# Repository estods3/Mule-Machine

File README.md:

# mule_machine
A drinkbot for making Moscow Mules

## Design File Structure

### SW
ATmega328 microcontroller code.
  * Pin Assignments
  * Bootup Animation
  * Standby Animation
  * Potentiometer Calibration Controls
  * Cup-Sensor Detection
  * Pump Control and LED animation

### HW

#### cad

Sketchup File - 3D model

LightBurn laser engraved part files (Coming Soon)

3D printed part files
* MM DRIP TRAY.STL 

#### pcb

Eagle Schematic file

Eagle board layout file

associated gerber files (manufacturing)

parts list/BOM

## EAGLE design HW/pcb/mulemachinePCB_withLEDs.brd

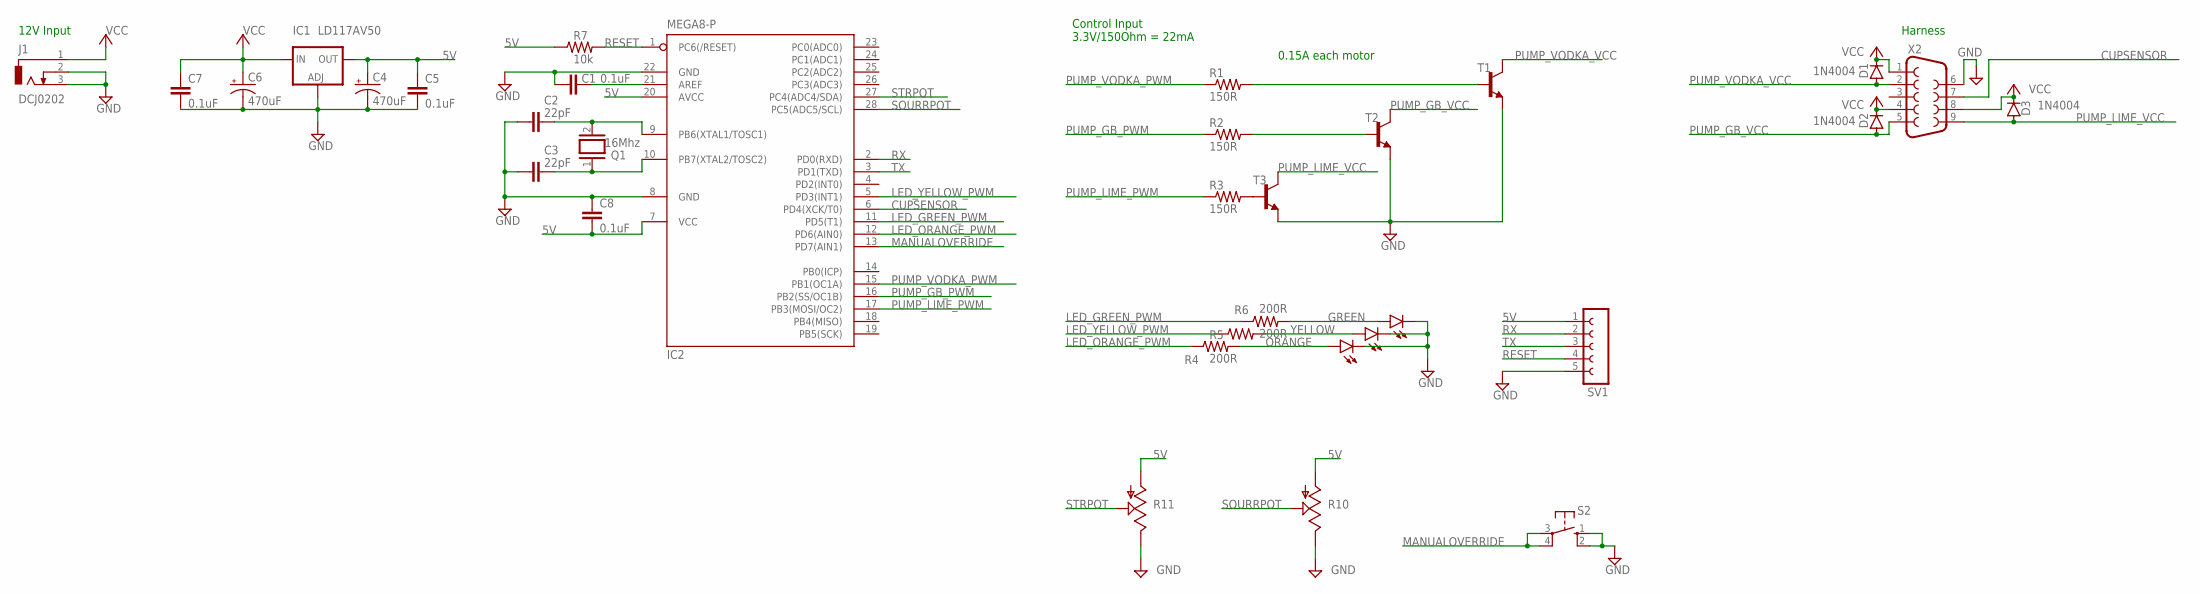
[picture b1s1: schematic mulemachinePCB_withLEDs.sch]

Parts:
C1, C5, C7, C8: 0.1uF; C2.5-3
C2, C3: 22pF; C2.5-3
C4, C6: 470uF; E2,5-6
D1, D2, D3: 1N4004; DO41-10
IC1: LD117AV50; TO220L1
IC2: MEGA8-P; DIL28-3
J1: DCJ0202
LED1, LED2, LED3: LED5MM
Q1: 16Mhz; QS
R1, R2, R3: 150R; 0411/12
R4, R5, R6: 200R; 0411/12
R7: 10k; 0207/10
R10, R11: US-EVUF3L; EVUFXL
S2: 10-XX; B3F-10XX
SV1: FE05-1
T1, T2, T3: 2N4401-NPN-TO92-EBC; TO92-EBC
X2: F09HP

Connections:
5V: C4.+, C5.1, C8.2, IC1.2 (OUT), IC2.7 (VCC), IC2.20 (AVCC), R7.1, R10.1 (A), R11.1 (A), SV1.1
CUPSENSOR: IC2.6 (PD4(XCK/T0)), X2.7
GND: C1.2, C2.2, C3.2, C4.-, C5.2, C6.-, C7.2, C8.1, IC1.1 (ADJ), IC2.8 (GND), IC2.22 (GND), J1.2, J1.3, LED1.K (C), LED2.K (C), LED3.K (C), R10.3 (E), R11.3 (E), S2.1 (S), S2.2 (S1), SV1.5, T1.E, T2.E, T3.E, X2.6
GREEN: LED3.A, R6.2
LED_GREEN_PWM: IC2.11 (PD5(T1)), R6.1
LED_ORANGE_PWM: IC2.12 (PD6(AIN0)), R4.1
LED_YELLOW_PWM: IC2.5 (PD3(INT1)), R5.1
MANUALOVERRIDE: IC2.13 (PD7(AIN1)), S2.3, S2.4 (P1)
unnamed: R3.2, T3.B
unnamed: R2.2, T2.B
unnamed: R1.2, T1.B
unnamed: C3.1, IC2.10 (PB7(XTAL2/TOSC2)), Q1.1
unnamed: C2.1, IC2.9 (PB6(XTAL1/TOSC1)), Q1.2
unnamed: C1.1, IC2.21 (AREF)
ORANGE: LED1.A, R4.2
PUMP_GB_PWM: IC2.16 (PB2(SS/OC1B)), R2.1
PUMP_GB_VCC: D2.A, T2.C, X2.5
PUMP_LIME_PWM: IC2.17 (PB3(MOSI/OC2)), R3.1
PUMP_LIME_VCC: D3.A, T3.C, X2.9
PUMP_VODKA_PWM: IC2.15 (PB1(OC1A)), R1.1
PUMP_VODKA_VCC: D1.A, T1.C, X2.2
RESET: IC2.1 (PC6(/RESET)), R7.2, SV1.4
RX: IC2.2 (PD0(RXD)), SV1.2
SOURRPOT: IC2.28 (PC5(ADC5/SCL)), R10.2 (S)
STRPOT: IC2.27 (PC4(ADC4/SDA)), R11.2 (S)
TX: IC2.3 (PD1(TXD)), SV1.3
VCC: C6.+, C7.1, D1.C, D2.C, D3.C, IC1.3 (IN), J1.1, X2.1, X2.4, X2.8
YELLOW: LED2.A, R5.2

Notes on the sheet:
12V Input
Harness
0.15A each motor
Control Input 3.3V/150Ohm = 22mA

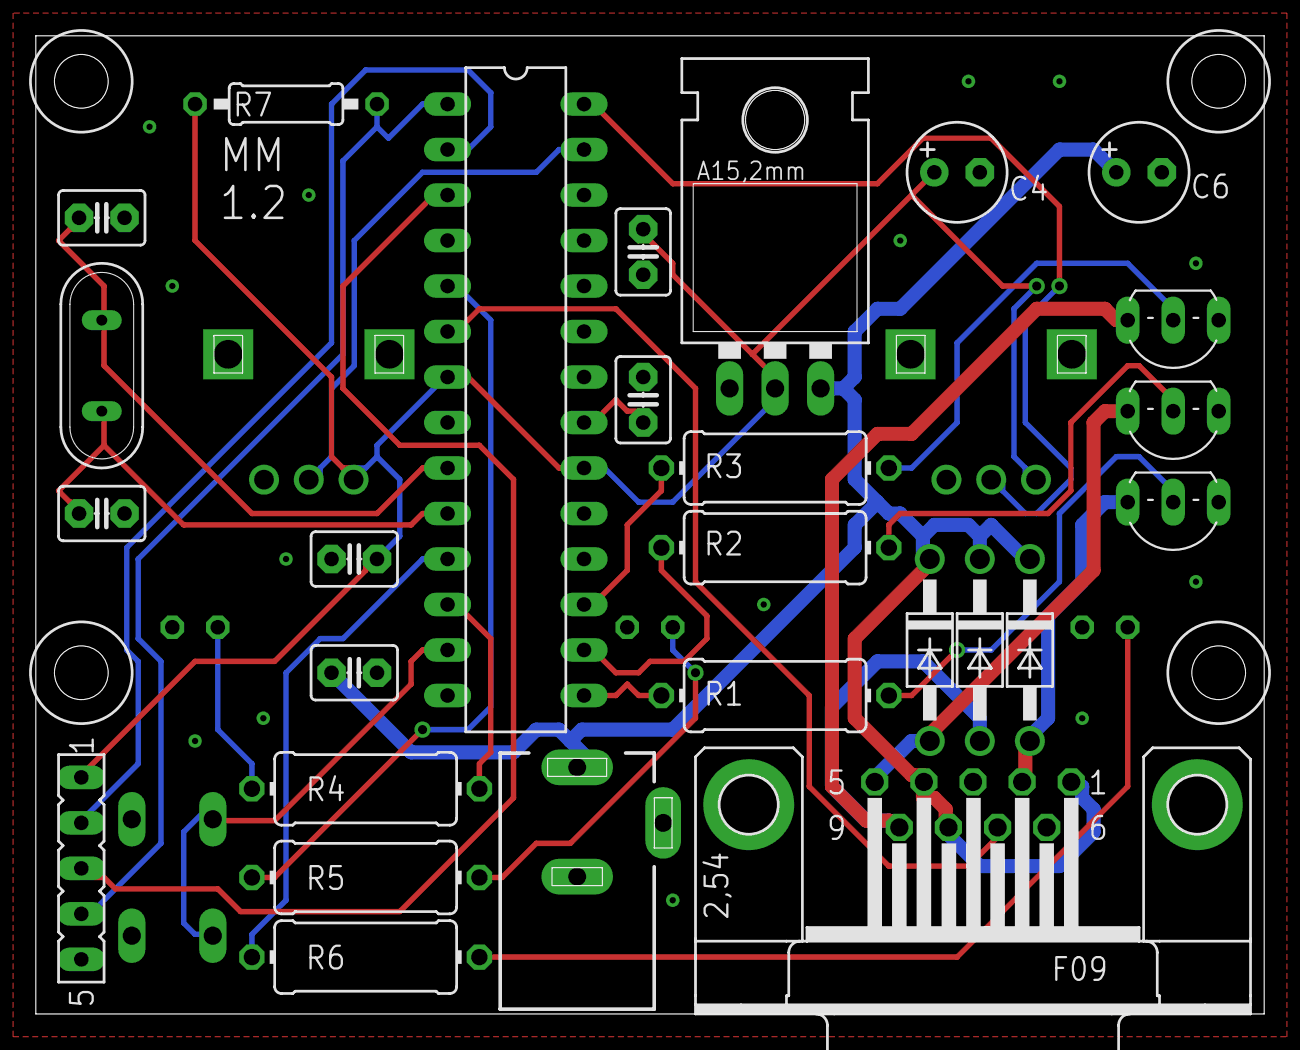
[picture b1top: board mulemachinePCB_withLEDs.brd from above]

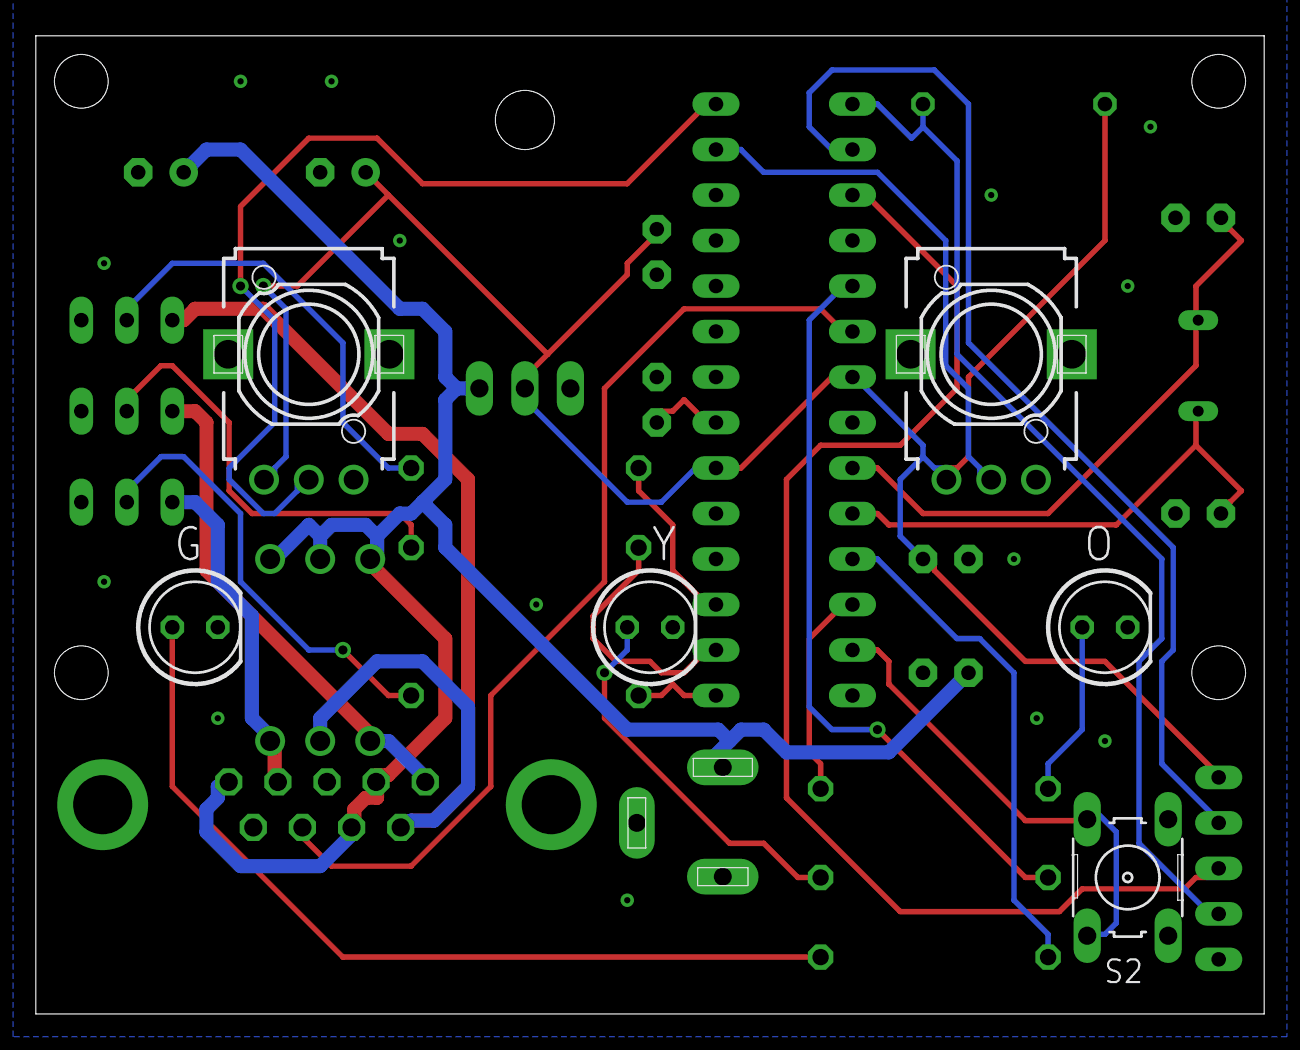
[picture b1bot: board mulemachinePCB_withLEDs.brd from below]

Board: 2 copper layers, 68.6 x 54.6 mm, 33 parts (6 on the bottom side), 28 nets.

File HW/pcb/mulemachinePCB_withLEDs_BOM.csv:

"Part";"Value";"Device";"Package";"Description";"MF";"MPN";"OC_FARNELL";"OC_NEWARK";"POPULARITY";"SPICEPREFIX";
"C1";"470uF";"C2,5-3";"C2.5-3";"CAPACITOR";"";"";"";"";"38";"";
"C2";"22pF";"C2,5-3";"C2.5-3";"CAPACITOR";"";"";"";"";"38";"";
"C3";"22pF";"C2,5-3";"C2.5-3";"CAPACITOR";"";"";"";"";"38";"";
"D1";"1N4004";"1N4004";"DO41-10";"DIODE";"";"";"";"";"82";"";
"D2";"1N4004";"1N4004";"DO41-10";"DIODE";"";"";"";"";"82";"";
"D3";"1N4004";"1N4004";"DO41-10";"DIODE";"";"";"";"";"82";"";
"IC1";"LD117AV50";"LD117AV50";"TO220L1";"Low drop fixed and adjustable positive voltage regulators 1 A";"";"";"";"";"0";"";
"IC2";"MEGA8-P";"MEGA8-P";"DIL28-3";"MICROCONTROLLER";"";"";"unknown";"unknown";"17";"";
"J1";"DCJ0202";"DCJ0202";"DCJ0202";"DC POWER JACK";"";"";"unknown";"unknown";"17";"";
"LED1";"";"LED5MM";"LED5MM";"LED";"";"";"";"";"93";"";
"LED2";"";"LED5MM";"LED5MM";"LED";"";"";"";"";"93";"";
"LED3";"";"LED5MM";"LED5MM";"LED";"";"";"";"";"93";"";
"Q1";"";"XTAL/S";"QS";"CRYSTAL";"";"";"";"";"59";"";
"R1";"150";"R-US_0204/7";"0204/7";"RESISTOR, American symbol";"";"";"";"";"48";"R";
"R2";"150";"R-US_0204/7";"0204/7";"RESISTOR, American symbol";"";"";"";"";"48";"R";
"R3";"150";"R-US_0204/7";"0204/7";"RESISTOR, American symbol";"";"";"";"";"48";"R";
"R4";"200";"R-US_0204/7";"0204/7";"RESISTOR, American symbol";"";"";"";"";"48";"R";
"R5";"200";"R-US_0204/7";"0204/7";"RESISTOR, American symbol";"";"";"";"";"48";"R";
"R6";"200";"R-US_0204/7";"0204/7";"RESISTOR, American symbol";"";"";"";"";"48";"R";
"R7";"200";"R-US_0204/7";"0204/7";"RESISTOR, American symbol";"";"";"";"";"48";"R";
"S1";"RDT1034";"RDT1034";"RDT1034";"PUSH SWITCH";"";"";"";"";"4";"";
"SV1";"";"FE05-1";"FE05-1";"FEMALE HEADER";"";"";"unknown";"unknown";"7";"";
"T1";"";"MPS2222A-NPN-TO92-CBE";"TO92-CBE";"NPN Transistror";"";"";"";"";"0";"";
"T2";"";"MPS2222A-NPN-TO92-CBE";"TO92-CBE";"NPN Transistror";"";"";"";"";"0";"";
"T3";"";"MPS2222A-NPN-TO92-CBE";"TO92-CBE";"NPN Transistror";"";"";"";"";"0";"";
"X2";"";"F09HP";"F09HP";"SUB-D";"";"";"unknown";"unknown";"2";"";

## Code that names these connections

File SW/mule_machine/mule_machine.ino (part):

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//Buttons, LEDs, Pumps
//HARDWARE: <MM1.1
//inputs
//const int cup_present_buttonPin = 5; //PD5, physical pin 11                 
//const int manual_override_button_pin = 6; //PD6, physical pin 12
//const int tuner_strength_pin = A4; //PC4, physical pin 27
//const int tuner_sour_pin = A5; //PC5, physical pin 28
////outputs
//const int ledGreen_Lime = 2; // PD2, physical pin 4
//const int ledYellow_GingerBeer = 3; // PD3, physical pin 5
//const int ledOrange_Vodka = 4; // PD4, physical pin 6
//const int pump_Vodka = A1; //PC1,A1, physical pin 24
//const int pump_GingerBeer = A2; //PC2,A2, physical pin 25
//const int pump_Lime =  A3; //PC3,A3, physical pin 26

//TODO HARDWARE: MM1.2, change to use real PWM not SoftPWM Lib
//inputs
const int cup_present_buttonPin = 4; //PD4, physical pin 6                 
const int manual_override_button_pin = 7; //PD7, physical pin 13
const int tuner_strength_pin = A4; //PC4, physical pin 27
const int tuner_sour_pin = A5; //PC5, physical pin 28
//outputs (PWM)
const int ledGreen_Lime = 5; // PD5, physical pin 11
const int ledYellow_GingerBeer = 3; // PD3, physical pin 5
const int ledOrange_Vodka = 6; // PD6, physical pin 12
const int pump_Vodka = 9; //PB1, physical pin 15
const int pump_GingerBeer = 10; //PB2, physical pin 16
const int pump_Lime =  11; //PB3, physical pin 17

//ANIMATION DELAYS
//Bootup, Standby Mode, Mixing Mode
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
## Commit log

2022-02-07 added PCB Eagle files
2022-02-07 added latest arduino code
2022-02-07 added Sketchup File. updated README.
2022-02-07 added folder structure to support Arduino IDE
2022-02-07 cleanup old pcd files
2022-02-09 implemented new calibration with pots. not yet tested on HW
2022-02-09 added laser files for front and sides. not yet finished
2022-02-12 finished layout for PCB. implemented trace widths for PWR and GND. Lined up hole placement to match with Front panel laser design.
2022-02-12 renamed MuleMachineCAD sketchup file
2022-02-12 finished preliminary design of front panel. need to determine assembly strategy for panels
2022-02-17 updated mule machine firmware to include better pot logic with rolling average (10 point). Tested on testbench with consistent results. Motors under load, Power consumption on standby was 0.8A @12V, 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
2022-02-17 ordered MM v1.0 of PCB. Gerber files contained in HW/pcb/mulemachinePCB_withLEDs_2022-02-17.zip
2022-02-24 fixed issue #7 on PCB. not yet ordered or tested on physical HW. schematic functionality should not change. just modified capacitor packaging
2022-02-24 fixed HMI to better match 300 degree pots from PCB
2022-02-25 saved
2022-03-01 changed hole sizes for PCB mounting holes. adjusted sizes of pot and LED holes based on a test print
2022-03-01 added offset to either side of laser front design to allow for slotted insert into sides
2022-03-01 first test of laser/front.lbrn2 file on 0.25 inch panel. Adjusted settings for text, image, holes, and title. all look good on test print. holes not all the way through wood.
2022-03-01 lowered speed/power for drill holes in laser CAD, as holes will not actually drill all the way through, and just serve as markings.
2022-03-01 fixed issue #8 where the transistor pinout was backwards. fixed for next PCB order
2022-03-11 changed resistor packaging to 0411/12 for new 100 and 200 ohm 2Watt resistors purchased.
2022-03-11 changed resistor packaging to 0411/12 for new 100 and 200 ohm 2Watt resistors purchased. change hole size (to 3mm) and spacing to match new pump mounting hole size for front panel.
2022-03-11 added gray outlines in panel for 6mm head size of new bolts.
2022-03-14 finished design of drip tray. imported into MuleMachineCAD file as component
2022-03-14 exported pngs of PCB design for documentation
2022-03-15 lowered pump atttachment points to make more room for copper nozzle. made seperate layer for front panel outline
2022-03-18 moved copper nozzle to be side-by-side with PCB UI. adds more height and uses the space better. added filled holed at center of each hole to make a divit for using a drill bit
2022-03-18 committing changes to PCB layout before changing db9 location
2022-03-24 preparing files for first prototype of version 1.0 of Mule Machine. Corrected Code to reflect Orange and Green LEDs being flipped on PCB and Code. Used PCB Version. Added some new design features to 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
2022-03-25 increased standby mode led delay to 25
2022-04-04 fixed #13 with additional 100uF cap on 12V power line and 0.1uF cap on 5v line in parallel with 470uF cap. This smooths the 12V line and the 5V line for more powerful motors. needs more duration of b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
2022-04-26 implemented manual override button logic into ATMEGA code
2022-04-26 sourced push button and added to schematic and PCB layout. matched needed mounting to laser front panel cutout.
2022-04-27 finished mating between front panel and PCB. routed PCB. PCB v1.1 is ready for gerber file generation and order.
2022-04-27 gerber files generated
2022-05-25 implemented new PWM logic to control motors. working version
2022-05-25 changed 12V side cap C6 to 470uF. rerouted board
2022-06-10 added comments. changed new cal input time to 600ms. increased ramp up and ramp down times for PCM. chip reset issue still prevelant
2022-09-20 added decoupling cap for MCU to schematic. organized schematic with groups
2022-09-21 rotated MCU to allow for better routing. added top and bottom layer ground planes with vias connecting them.
2022-09-21 adjusted net classes so that pump VCCs lines were also considered power traces (wider). rerouted and adjusted GND planes
2022-09-21 repinned LED and pump pins on MCU to use PWM digital pins. need to check and then reroute PCB and redo GND planes
2022-09-21 reorganized MCU code. added a function for LED animations to clean up code. re-wrote analog moving filter functions to recompute total each run using array for() loop. need to test
2022-09-21 finished positioning components, rerouted and made ground planes
2022-09-21 finished positioning components, rerouted and made ground planes, added GND plane vias
2022-10-07 updated code to include functions for LED animations. Tested on PCBs MMv1.1. working correctly, still experiencing issue #13 but not as frequently. MM can run for 30s+ before restarting
2022-10-07 updates to front laser design
2022-10-17 improved drip tray. reduced size, added T-Slot mounts.
2022-11-04 added 3mm holes for T slot mounts to front panel
2022-11-04 updated manufacturing PCB images for README. updated gerber files
2022-11-04 moved Y label for yellow LED on PCB. remake gerber files
2022-11-05 fixed issue with mismatch in names for orange LED signal PWM signal name. corrected, regenerated CAM data, reordered PCBs, and remade PNGs
2022-12-03 misc changes to laser program
2022-12-03 added analogWrite() function calls for native PWM pins instead of using softPWM library. test on MM1.2 HW. working with LEDs not tested with pump harness. Observation: when in standby after power up 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
2023-02-25 fixed @21. added analogWrite(pump_*, 0) after while() loop to turn off pumps after exiting Mixing Mode
2023-02-25 fixed #21. added analogWrite(pump_*, 0) after while() loop to turn off pumps after exiting Mixing Mode
2023-10-10 added deadzone logic for motors. added mode to support 2 motors for ginger beer ingredient which allows for faster operation.
